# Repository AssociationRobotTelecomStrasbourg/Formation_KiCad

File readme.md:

#Formation KiCad

####Description des fichiers

Ce repo contient les deux formations KiCad rédigées au sein de l'association.

La formation **Servoboard** est plus adaptée à un novice, car beaucoup plus guidée.
Il s'agit de concevoir une petit carte mère pouvant accueillir une Arduino Nano et un Servo-moteur SG-90.

La formation **NE555** tourne autour du composant *NE555*, comme le nom l'indique. Il s'agit de concevoir un circuit entièrement analogique permettant de faire clignoter des LEDs.
Le dossier contient la fichie technique du composant, ainsi, qu'un projet KiCad contenant un schèma à compléter, et un autre complet.

Le sujet de chaque formation est disponible dans chacun des dossiers.<
#####

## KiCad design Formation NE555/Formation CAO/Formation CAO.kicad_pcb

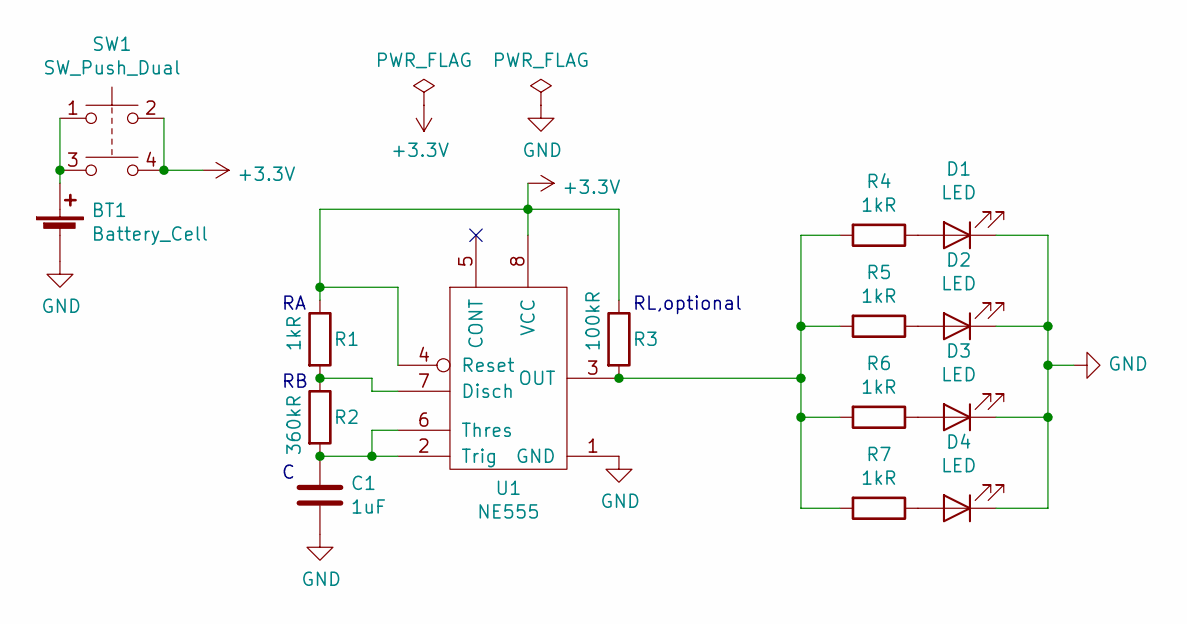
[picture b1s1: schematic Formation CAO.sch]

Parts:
BT1: Battery_Cell; BatteryHolder_Keystone_103_1x20mm
C1: 1uF; CP_Radial_D5.0mm_P2.50mm
D1, D2, D3, D4: LED; LED_D5.0mm
R1: 1kR; R_Axial_DIN0204_L3.6mm_D1.6mm_P5.08mm_Horizontal
R2: 360kR; R_Axial_DIN0204_L3.6mm_D1.6mm_P5.08mm_Horizontal
R3: 100kR; R_Axial_DIN0204_L3.6mm_D1.6mm_P5.08mm_Horizontal
R4, R5, R6, R7: 1kR; R_1206_3216Metric_Pad1.42x1.75mm_HandSolder
SW1: SW_Push_Dual; SW_Push_1P1T_NO_6x6mm_H9.5mm
U1: NE555; DIP-8_W7.62mm_LongPads

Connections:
+3V3: R1.1, R3.1, SW1.2, SW1.4, U1.4 (Reset), U1.8 (VCC)
GND: BT1.2 (-), C1.2, D1.1 (K), D2.1 (K), D3.1 (K), D4.1 (K), U1.1 (GND)
unnamed: BT1.1 (+), SW1.1, SW1.3
unnamed: C1.1, R2.2, U1.2 (Trig), U1.6 (Thres)
unnamed: D1.2 (A), R4.1
unnamed: D2.2 (A), R5.1
unnamed: D3.2 (A), R6.1
unnamed: D4.2 (A), R7.1
unnamed: R1.2, R2.1, U1.7 (Disch)
unnamed: R3.2, R4.2, R5.2, R6.2, R7.2, U1.3 (OUT)

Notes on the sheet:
RL,optional

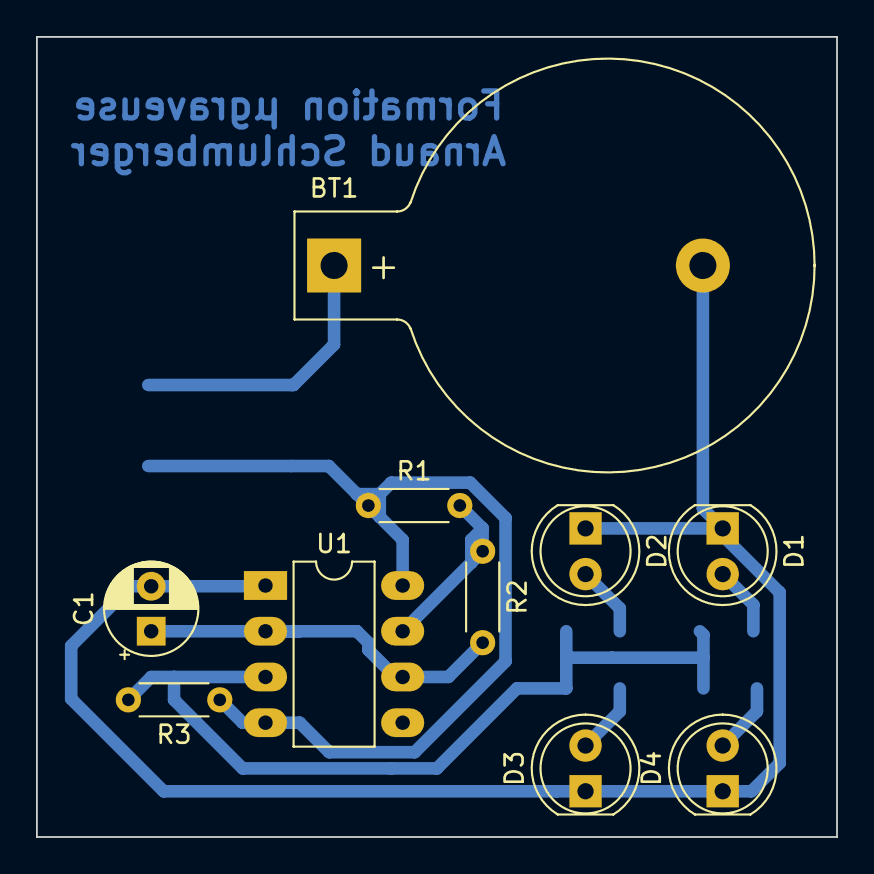
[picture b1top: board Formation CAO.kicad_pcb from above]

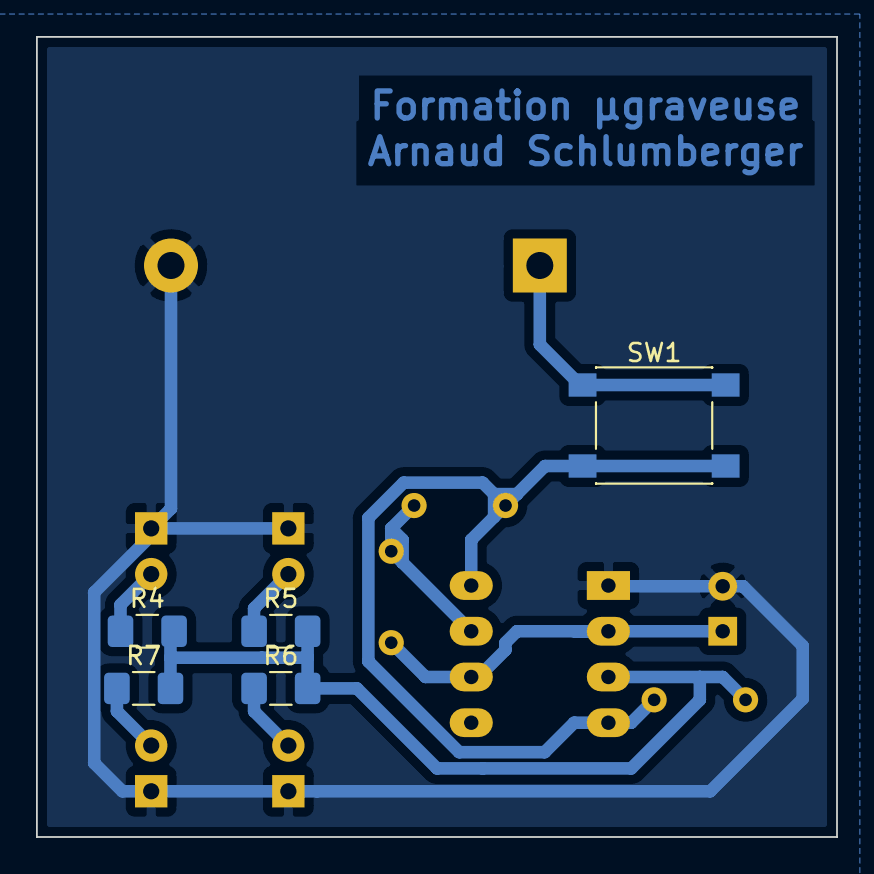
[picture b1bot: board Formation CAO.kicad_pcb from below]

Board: 2 copper layers, 44.4 x 44.5 mm, 15 parts (5 on the bottom side), 10 nets.

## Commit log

2020-11-09 Creation du dossier
2020-11-09 Ajout readme
